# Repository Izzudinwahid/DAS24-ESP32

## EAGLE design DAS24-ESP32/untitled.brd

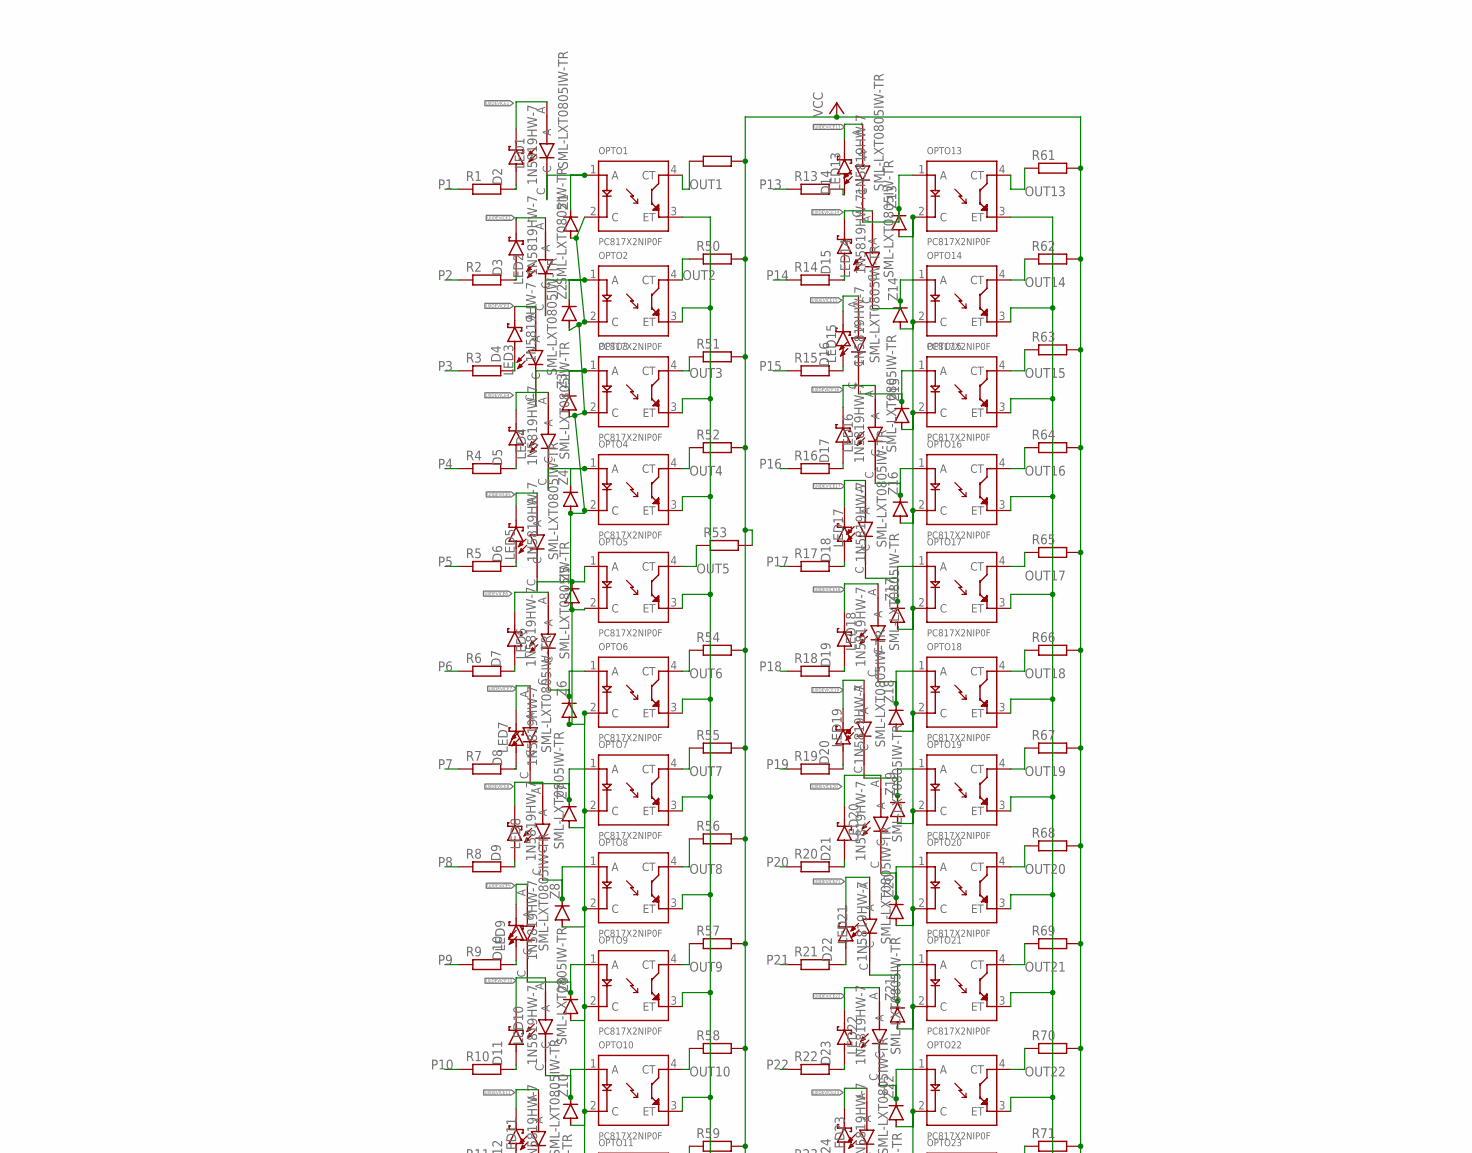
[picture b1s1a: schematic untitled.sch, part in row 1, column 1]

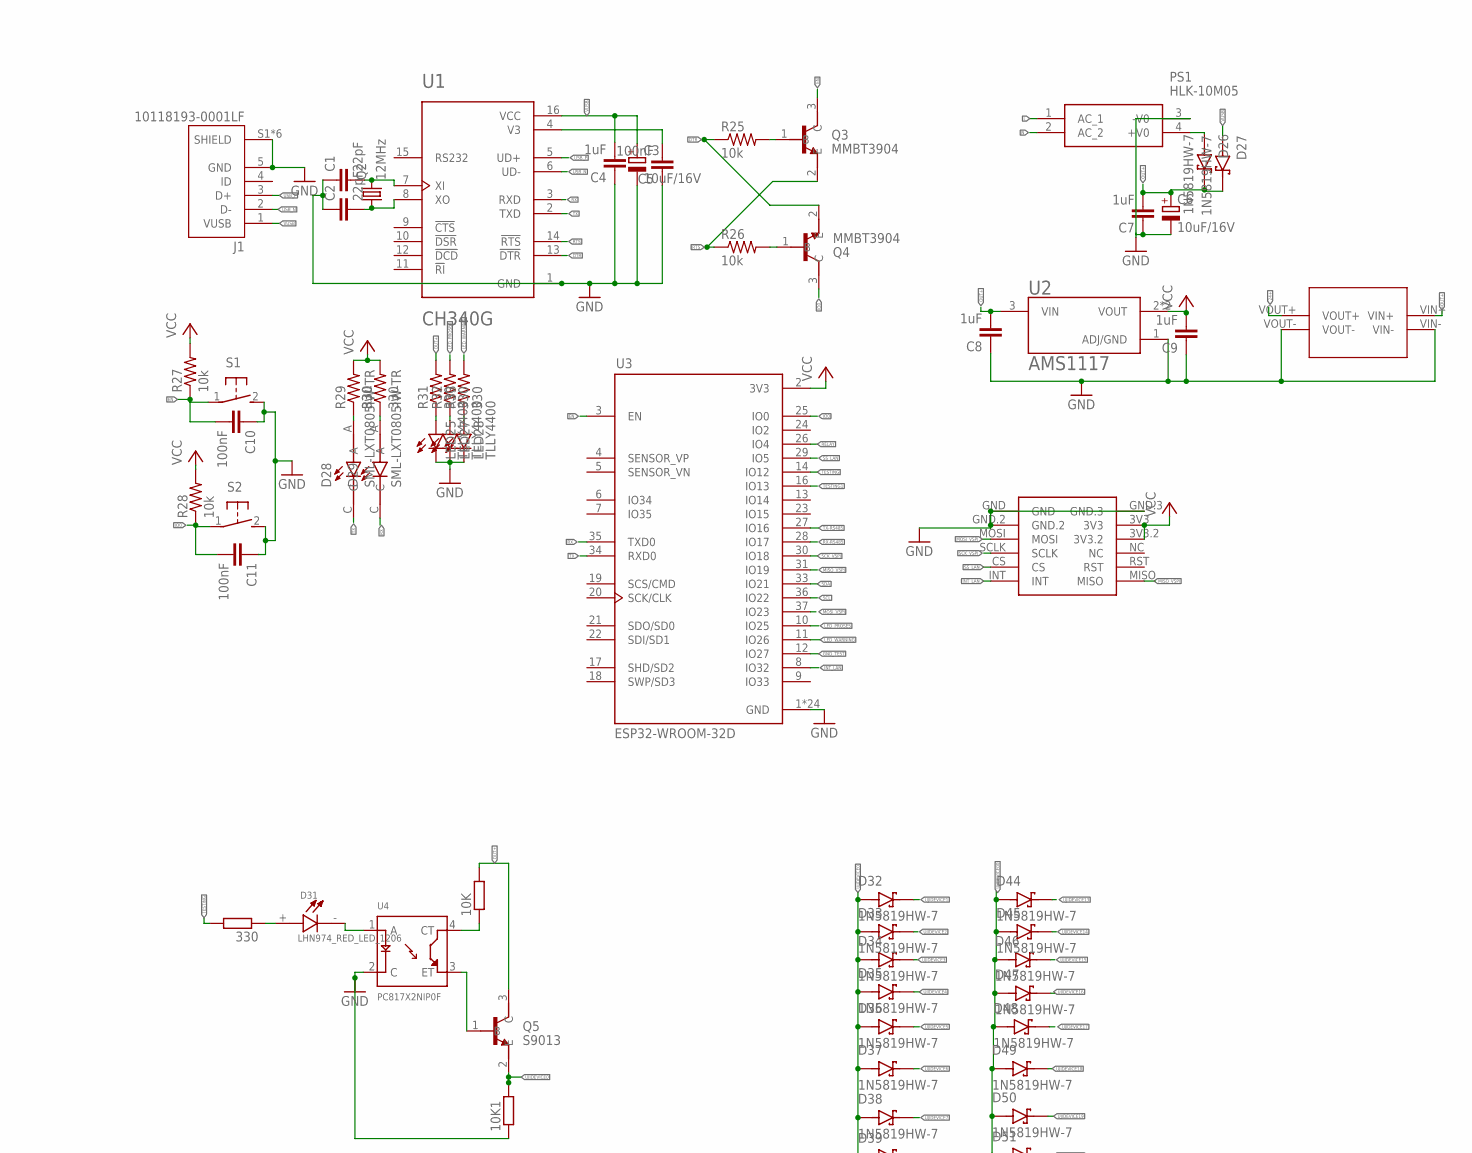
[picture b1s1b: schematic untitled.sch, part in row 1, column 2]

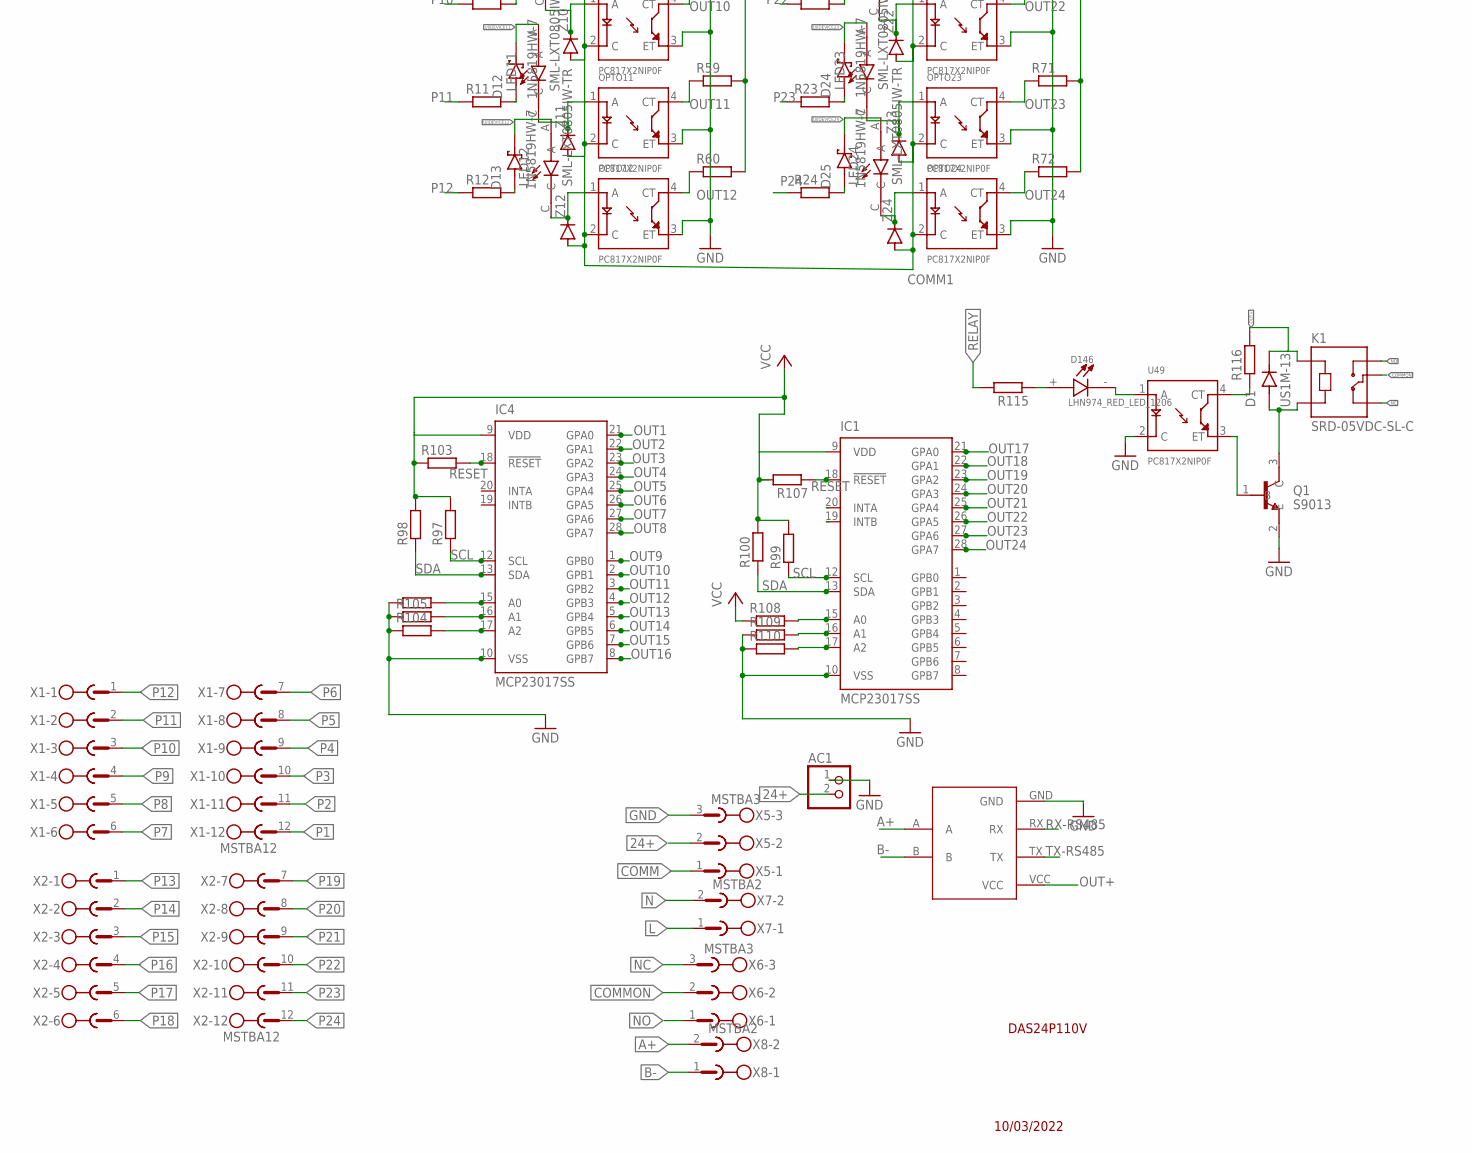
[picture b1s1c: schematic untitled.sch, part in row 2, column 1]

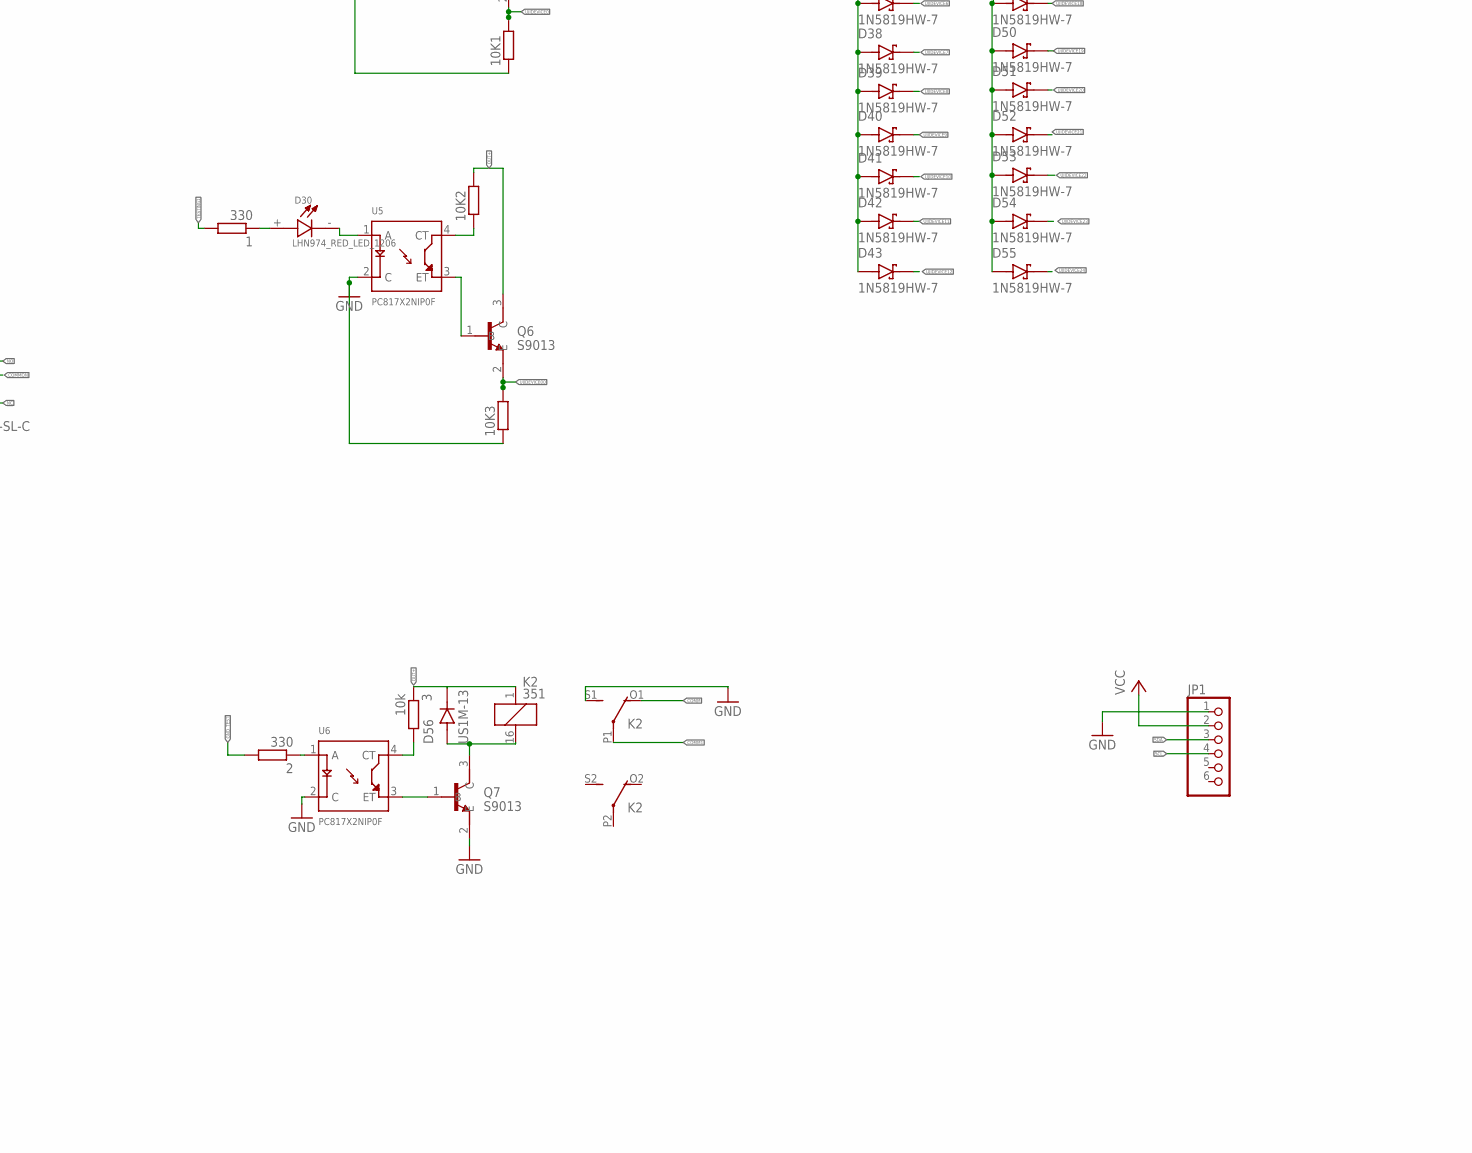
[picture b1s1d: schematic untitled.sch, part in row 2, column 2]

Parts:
1, 2: 330; R0805
3: 10k; R0805
10K, 10K1, 10K2, 10K3, 330: R-EU_R0805; R0805
AC1: PINHD-1X2; 1X02
C1, C2: 22pF; C0805K
C3, C6: 10uF/16V; 153CLV-0505
C4, C7, C8, C9: 1uF; C0805K
C5, C10, C11: 100nF; C0805K
D1, D56: US1M-13; DIOM5226X240N
D2, D3, D4, D5, D6, D7, D8, D9, D10, D11, D12, D13, D14, D15, D16, D17, D18, D19, D20, D21, D22, D23, D24, D25, D26, D27, D32, D33, D34, D35, D36, D37, D38, D39, D40, D41, D42, D43, D44, D45, D46, D47, D48, D49, D50, D51, D52, D53, D54, D55: 1N5819HW-7; SOD3715X145N
D28, D29: SML-LXT0805IW-TR; LEDC2012X120N
D30, D31, D146: LHN974_RED_LED_1206; LEDC3216X120N
IC1, IC4: MCP23017SS; SSOP28DB
J1: 10118193-0001LF; FCI_10118193-0001LF
JP1: PINHD-1X6CLEAN; 1X06-CLEAN
K1: SRD-05VDC-SL-C; RELAY_SRD-05VDC-SL-C
K2: 351
LED1, LED2, LED3, LED4, LED5, LED6, LED7, LED8, LED9, LED10, LED11, LED12, LED13, LED14, LED15, LED16, LED17, LED18, LED19, LED20, LED21, LED22, LED23, LED24: SML-LXT0805IW-TR; LEDC2012X120N
LED25, LED27, LED28: TLLY4400; LED3MM
MT1: MT3608
OPTO1, OPTO2, OPTO3, OPTO4, OPTO5, OPTO6, OPTO7, OPTO8, OPTO9, OPTO10, OPTO11, OPTO12, OPTO13, OPTO14, OPTO15, OPTO16, OPTO17, OPTO18, OPTO19, OPTO20, OPTO21, OPTO22, OPTO23, OPTO24: PC817X2NIP0F; SOT254P975X400-4N
PS1: HLK-10M05; HLK10M05
Q1, Q5, Q6, Q7: S9013; SOT95P240X120-3N
Q2: 12MHz; SM49
Q3, Q4: MMBT3904; SOT95P240X120-3N
R1, R2, R3, R4, R5, R6, R7, R8, R9, R10, R11, R12, R13, R14, R15, R16, R17, R18, R19, R20, R21, R22, R23, R24: R-EU_0414/15; 0414/15
R25, R26, R27, R28: 10k; M0805
R29, R30, R31, R32, R33: 330; M0805
R49, R50, R51, R52, R53, R54, R55, R56, R57, R58, R59, R60, R61, R62, R63, R64, R65, R66, R67, R68, R69, R70, R71, R72, R97, R98, R99, R100, R103, R104, R105, R106, R107, R108, R109, R110, R115, R116: R-EU_R0805; R0805
S1, S2: 31-XX; B3F-31XX
TTL-RS1: TTL-RS485
U1: CH340G; SOIC127P600X180-16N
U2: AMS1117; SOT229P700X180-4N
U3: ESP32-WROOM-32D; MODULE_ESP32-WROOM-32D
U4, U5, U6, U49: PC817X2NIP0F; SOT254P975X400-4N
U$1: MINI_W5500
X1, X2: MSTBA12
X5, X6: MSTBA3
X7, X8: MSTBA2
Z1, Z2, Z3, Z4, Z5, Z6, Z7, Z8, Z9, Z10, Z11, Z12, Z13, Z14, Z15, Z16, Z17, Z18, Z19, Z20, Z21, Z22, Z23, Z24: DIODE-SOD123; SOD123

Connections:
24+: AC1.2, MT1.VOUT+, X5.2
A+: TTL-RS1.A, X8.2
B-: TTL-RS1.B, X8.1
COMM: K2.O1 (O), X5.1
COMM1: K2.P1, OPTO1.2 (C), OPTO2.2 (C), OPTO3.2 (C), OPTO4.2 (C), OPTO5.2 (C), OPTO6.2 (C), OPTO7.2 (C), OPTO8.2 (C), OPTO9.2 (C), OPTO10.2 (C), OPTO11.2 (C), OPTO12.2 (C), OPTO13.2 (C), OPTO14.2 (C), OPTO15.2 (C), OPTO16.2 (C), OPTO17.2 (C), OPTO18.2 (C), OPTO19.2 (C), OPTO20.2 (C), OPTO21.2 (C), OPTO22.2 (C), OPTO23.2 (C), OPTO24.2 (C), Z1.A, Z2.A, Z3.A, Z4.A, Z5.A, Z6.A, Z7.A, Z8.A, Z9.A, Z10.A, Z11.A, Z12.A, Z13.A, Z14.A, Z15.A, Z16.A, Z17.A, Z18.A, Z19.A, Z20.A, Z21.A, Z22.A, Z23.A, Z24.A
COMMON: K1.COM, X6.2
DTR: Q4.2 (E), R25.1, U1.13 (!DTR)
EN: C10.2, Q3.3 (C), R27.1, S1.1, U3.3 (EN)
GND: 10K1.1, 10K3.1, AC1.1, C1.1, C2.1, C3.-, C4.1, C5.1, C6.-, C7.1, C8.1, C9.1, C10.1, C11.1, IC1.10 (VSS), IC4.10 (VSS), J1.5 (GND), J1.S1 (SHIELD), J1.S2 (SHIELD), J1.S3 (SHIELD), J1.S4 (SHIELD), J1.S5 (SHIELD), J1.S6 (SHIELD), JP1.1, K2.S1 (S), LED25.K (C), LED27.K (C), LED28.K (C), MT1.VIN-, MT1.VOUT-, OPTO1.3 (ET), OPTO2.3 (ET), OPTO3.3 (ET), OPTO4.3 (ET), OPTO5.3 (ET), OPTO6.3 (ET), OPTO7.3 (ET), OPTO8.3 (ET), OPTO9.3 (ET), OPTO10.3 (ET), OPTO11.3 (ET), OPTO12.3 (ET), OPTO13.3 (ET), OPTO14.3 (ET), OPTO15.3 (ET), OPTO16.3 (ET), OPTO17.3 (ET), OPTO18.3 (ET), OPTO19.3 (ET), OPTO20.3 (ET), OPTO21.3 (ET), OPTO22.3 (ET), OPTO23.3 (ET), OPTO24.3 (ET), PS1.3 (-V0), Q1.2 (E), Q7.2 (E), R104.1, R105.1, R106.1, R109.1, R110.1, S1.2 (S), S2.2 (S), TTL-RS1.GND, U1.1 (GND), U2.1 (ADJ/GND), U3.1 (GND), U3.15 (GND), U3.38 (GND), U3.39_1 (GND), U3.39_2 (GND), U3.39_3 (GND), U3.39_4 (GND), U3.39_5 (GND), U3.39_6 (GND), U3.39_7 (GND), U3.39_8 (GND), U3.39_9 (GND), U3.39_10 (GND), U3.39_11 (GND), U3.39_12 (GND), U3.39_13 (GND), U3.39_14 (GND), U3.39_15 (GND), U3.39_16 (GND), U3.39_17 (GND), U3.39_18 (GND), U3.39_19 (GND), U3.39_20 (GND), U3.39_21 (GND), U4.2 (C), U5.2 (C), U6.2 (C), U49.2 (C), U$1.GND, U$1.GND.2, U$1.GND.3, X5.3
GND_TEST: 2.2, U3.12 (IO27)
INT_LAN: U3.8 (IO32), U$1.INT
IO0: C11.2, Q4.3 (C), R28.1, S2.1, U3.25 (IO0)
L: PS1.1 (AC_1), X7.1
LED_PROSES: R32.2, U3.10 (IO25)
LED_WARNING: R33.2, U3.11 (IO26)
MISO_VSPI: U3.31 (IO19), U$1.MISO
MOSI_VSPI: U3.37 (IO23), U$1.MOSI
N: PS1.2 (AC_2), X7.2
unnamed: D2.A, R1.2
unnamed: LED10.C, OPTO10.1 (A), Z10.C
unnamed: D3.A, R2.2
unnamed: D4.A, R3.2
unnamed: LED1.C, OPTO1.1 (A), Z1.C
unnamed: D5.A, R4.2
unnamed: LED27.A, R32.1
unnamed: D6.A, R5.2
unnamed: LED28.A, R33.1
unnamed: D7.A, R6.2
unnamed: LED2.C, OPTO2.1 (A), Z2.C
unnamed: D8.A, R7.2
unnamed: 2.1, U6.1 (A)
unnamed: D9.A, R8.2
unnamed: LED3.C, OPTO3.1 (A), Z3.C
unnamed: D15.A, R14.2
unnamed: 3.2, U6.4 (CT)
unnamed: LED4.C, OPTO4.1 (A), Z4.C
unnamed: D10.A, R9.2
unnamed: LED5.C, OPTO5.1 (A), Z5.C
unnamed: D56.A, K2.16 (2), Q7.3 (C)
unnamed: D11.A, R10.2
unnamed: Q7.1 (B), U6.3 (ET)
unnamed: LED6.C, OPTO6.1 (A), Z6.C
unnamed: C1.2, Q2.2, U1.7 (XI)
unnamed: D12.A, R11.2
unnamed: C2.2, Q2.1, U1.8 (XO)
unnamed: Q3.1 (B), R25.2
unnamed: C5.2, U1.4 (V3)
unnamed: Q4.1 (B), R26.2
unnamed: D26.A, PS1.4 (+V0)
unnamed: 330.1, D31.+
unnamed: D13.A, R12.2
unnamed: LED25.A, R31.1
unnamed: D28.A, R29.1
unnamed: D29.A, R30.1
unnamed: D14.A, R13.2
unnamed: 1.1, D30.+
unnamed: D31.-, U4.1 (A)
unnamed: 10K.1, U4.4 (CT)
unnamed: D16.A, R15.2
unnamed: Q5.1 (B), U4.3 (ET)
unnamed: D30.-, U5.1 (A)
unnamed: 10K2.1, U5.4 (CT)
unnamed: D17.A, R16.2
unnamed: D18.A, R17.2
unnamed: D19.A, R18.2
unnamed: D20.A, R19.2
unnamed: D21.A, R20.2
unnamed: LED7.C, OPTO7.1 (A), Z7.C
unnamed: D22.A, R21.2
unnamed: LED8.C, OPTO8.1 (A), Z8.C
unnamed: LED9.C, OPTO9.1 (A), Z9.C
unnamed: LED11.C, OPTO11.1 (A), Z11.C
unnamed: LED12.C, OPTO12.1 (A), Z12.C
unnamed: D23.A, R22.2
unnamed: LED13.C, OPTO13.1 (A), Z13.C
unnamed: LED14.C, OPTO14.1 (A), Z14.C
unnamed: LED15.C, OPTO15.1 (A), Z15.C
unnamed: D24.A, R23.2
unnamed: LED16.C, OPTO16.1 (A), Z16.C
unnamed: LED17.C, OPTO17.1 (A), Z17.C
unnamed: LED18.C, OPTO18.1 (A), Z18.C
unnamed: D25.A, R24.2
unnamed: LED19.C, OPTO19.1 (A), Z19.C
unnamed: LED20.C, OPTO20.1 (A), Z20.C
unnamed: LED21.C, OPTO21.1 (A), Z21.C
unnamed: LED22.C, OPTO22.1 (A), Z22.C
unnamed: LED23.C, OPTO23.1 (A), Z23.C
unnamed: LED24.C, OPTO24.1 (A), Z24.C
unnamed: Q6.1 (B), U5.3 (ET)
unnamed: D146.-, U49.1 (A)
unnamed: D146.+, R115.1
unnamed: R116.1, U49.4 (CT)
unnamed: D1.A, K1.A2, Q1.3 (C)
unnamed: Q1.1 (B), U49.3 (ET)
unnamed: IC1.15 (A0), R108.2
unnamed: IC1.16 (A1), R109.2
unnamed: IC4.15 (A0), R106.2
unnamed: IC4.16 (A1), R105.2
unnamed: IC4.17 (A2), R104.2
unnamed: IC1.17 (A2), R110.2
NC: K1.NC, X6.3
NO: K1.NO, X6.1
OUT1: IC4.21 (GPA0), OPTO1.4 (CT), R49.1
OUT2: IC4.22 (GPA1), OPTO2.4 (CT), R50.1
OUT3: IC4.23 (GPA2), OPTO3.4 (CT), R51.1
OUT4: IC4.24 (GPA3), OPTO4.4 (CT), R52.1
OUT5: IC4.25 (GPA4), OPTO5.4 (CT), R53.1
OUT6: IC4.26 (GPA5), OPTO6.4 (CT), R54.1
OUT7: IC4.27 (GPA6), OPTO7.4 (CT), R55.1
OUT8: IC4.28 (GPA7), OPTO8.4 (CT), R56.1
OUT9: IC4.1 (GPB0), OPTO9.4 (CT), R57.1
OUT10: IC4.2 (GPB1), OPTO10.4 (CT), R58.1
OUT11: IC4.3 (GPB2), OPTO11.4 (CT), R59.1
OUT12: IC4.4 (GPB3), OPTO12.4 (CT), R60.1
OUT13: IC4.5 (GPB4), OPTO13.4 (CT), R61.1
OUT14: IC4.6 (GPB5), OPTO14.4 (CT), R62.1
OUT15: IC4.7 (GPB6), OPTO15.4 (CT), R63.1
OUT16: IC4.8 (GPB7), OPTO16.4 (CT), R64.1
OUT17: IC1.21 (GPA0), OPTO17.4 (CT), R65.1
OUT18: IC1.22 (GPA1), OPTO18.4 (CT), R66.1
OUT19: IC1.23 (GPA2), OPTO19.4 (CT), R67.1
OUT20: IC1.24 (GPA3), OPTO20.4 (CT), R68.1
OUT21: IC1.25 (GPA4), OPTO21.4 (CT), R69.1
OUT22: IC1.26 (GPA5), OPTO22.4 (CT), R70.1
OUT23: IC1.27 (GPA6), OPTO23.4 (CT), R71.1
OUT24: IC1.28 (GPA7), OPTO24.4 (CT), R72.1
OUT+: 3.1, 10K.2, 10K2.2, C6.+, C7.2, C8.2, D1.C (K), D26.C (K), D27.C (K), D56.C (K), K1.A1, K2.1, MT1.VIN+, Q5.3 (C), Q6.3 (C), R31.2, R116.2, TTL-RS1.VCC, U2.3 (VIN)
P1: R1.1, X1.12
P2: R2.1, X1.11
P3: R3.1, X1.10
P4: R4.1, X1.9
P5: R5.1, X1.8
P6: R6.1, X1.7
P7: R7.1, X1.6
P8: R8.1, X1.5
P9: R9.1, X1.4
P10: R10.1, X1.3
P11: R11.1, X1.2
P12: R12.1, X1.1
P13: R13.1, X2.1
P14: R14.1, X2.2
P15: R15.1, X2.3
P16: R16.1, X2.4
P17: R17.1, X2.5
P18: R18.1, X2.6
P19: R19.1, X2.7
P20: R20.1, X2.8
P21: R21.1, X2.9
P22: R22.1, X2.10
P23: R23.1, X2.11
P24: R24.1, X2.12
RELAY: R115.2, U3.26 (IO4)
RESET: IC1.18 (!RESET), IC4.18 (!RESET), R103.2, R107.1
RTS: Q3.2 (E), R26.1, U1.14 (!RTS)
RX: D29.C, U1.3 (RXD), U3.35 (TXD0)
RX-RS485: TTL-RS1.RX, U3.28 (IO17)
SCK_VSPI: U3.30 (IO18), U$1.SCLK
SCL: IC1.12 (SCL), IC4.12 (SCL), JP1.4, R97.1, R99.1, U3.36 (IO22)
SDA: IC1.13 (SDA), IC4.13 (SDA), JP1.3, R98.1, R100.1, U3.33 (IO21)
SS_LAN: U3.29 (IO5), U$1.CS
TESTING: 330.2, U3.14 (IO12)
TESTING1: 1.2, U3.16 (IO13)
TX: D28.C, U1.2 (TXD), U3.34 (RXD0)
TX-RS485: TTL-RS1.TX, U3.27 (IO16)
UJIDEVICE0: 10K1.2, D32.A, D33.A, D34.A, D35.A, D36.A, D37.A, D38.A, D39.A, D40.A, D41.A, D42.A, D43.A, Q5.2 (E)
UJIDEVICE00: 10K3.2, D44.A, D45.A, D46.A, D47.A, D48.A, D49.A, D50.A, D51.A, D52.A, D53.A, D54.A, D55.A, Q6.2 (E)
UJIDEVICE1: D2.C (K), D32.C (K), LED1.A
UJIDEVICE2: D3.C (K), D33.C (K), LED2.A
UJIDEVICE3: D4.C (K), D34.C (K), LED3.A
UJIDEVICE4: D5.C (K), D35.C (K), LED4.A
UJIDEVICE5: D6.C (K), D36.C (K), LED5.A
UJIDEVICE6: D7.C (K), D37.C (K), LED6.A
UJIDEVICE7: D8.C (K), D38.C (K), LED7.A
UJIDEVICE8: D9.C (K), D39.C (K), LED8.A
UJIDEVICE9: D10.C (K), D40.C (K), LED9.A
UJIDEVICE10: D11.C (K), D41.C (K), LED10.A
UJIDEVICE11: D12.C (K), D42.C (K), LED11.A
UJIDEVICE12: D13.C (K), D43.C (K), LED12.A
UJIDEVICE13: D14.C (K), D44.C (K), LED13.A
UJIDEVICE14: D15.C (K), D45.C (K), LED14.A
UJIDEVICE15: D16.C (K), D46.C (K), LED15.A
UJIDEVICE16: D17.C (K), D47.C (K), LED16.A
UJIDEVICE17: D18.C (K), D48.C (K), LED17.A
UJIDEVICE18: D19.C (K), D49.C (K), LED18.A
UJIDEVICE19: D20.C (K), D50.C (K), LED19.A
UJIDEVICE20: D21.C (K), D51.C (K), LED20.A
UJIDEVICE21: D22.C (K), D52.C (K), LED21.A
UJIDEVICE22: D23.C (K), D53.C (K), LED22.A
UJIDEVICE23: D24.C (K), D54.C (K), LED23.A
UJIDEVICE24: D25.C (K), D55.C (K), LED24.A
USB_N: J1.2 (D-), U1.6 (UD-)
USB_P: J1.3 (D+), U1.5 (UD+)
VCC: C9.2, IC1.9 (VDD), IC4.9 (VDD), JP1.2, R27.2, R28.2, R29.2, R30.2, R49.2, R50.2, R51.2, R52.2, R53.2, R54.2, R55.2, R56.2, R57.2, R58.2, R59.2, R60.2, R61.2, R62.2, R63.2, R64.2, R65.2, R66.2, R67.2, R68.2, R69.2, R70.2, R71.2, R72.2, R97.2, R98.2, R99.2, R100.2, R103.1, R107.2, R108.1, U2.2 (VOUT), U2.4 (VOUT), U3.2 (3V3), U$1.3V3, U$1.3V3.2
VUSB: C3.+, C4.2, D27.A, J1.1 (VUSB), U1.16 (VCC)

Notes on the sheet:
DAS24P110V
10/03/2022

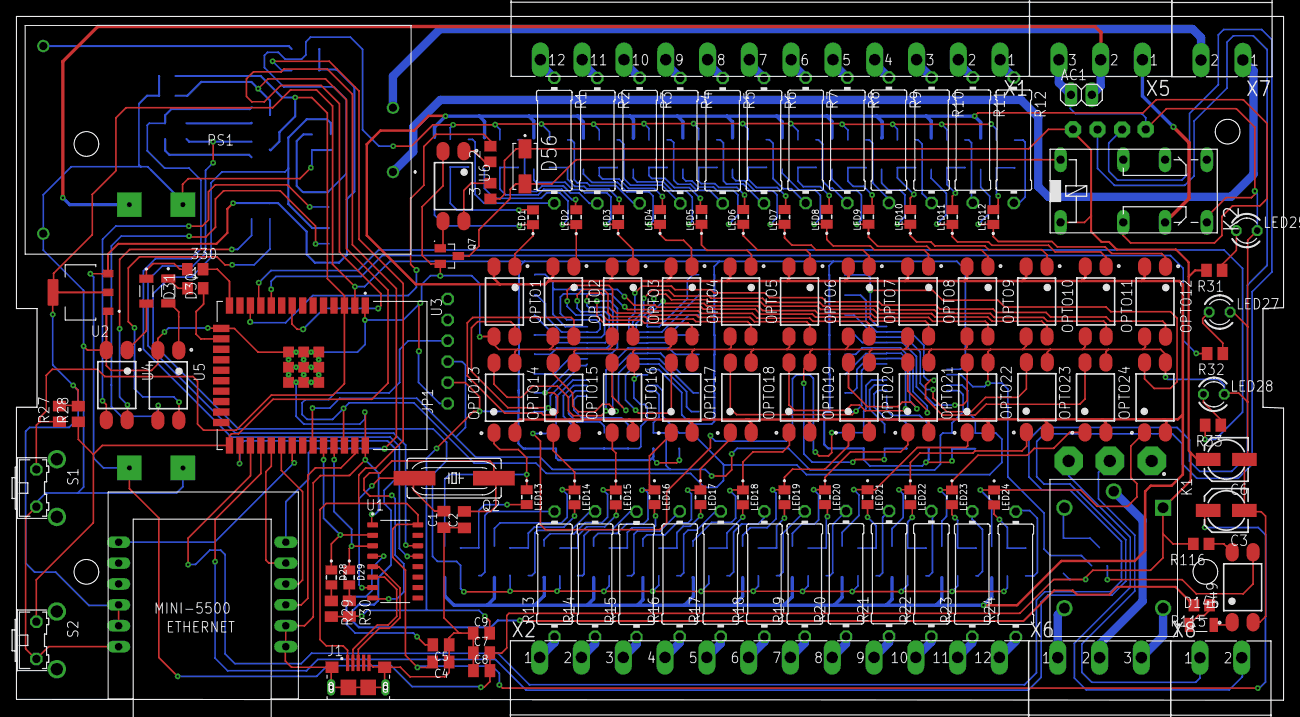
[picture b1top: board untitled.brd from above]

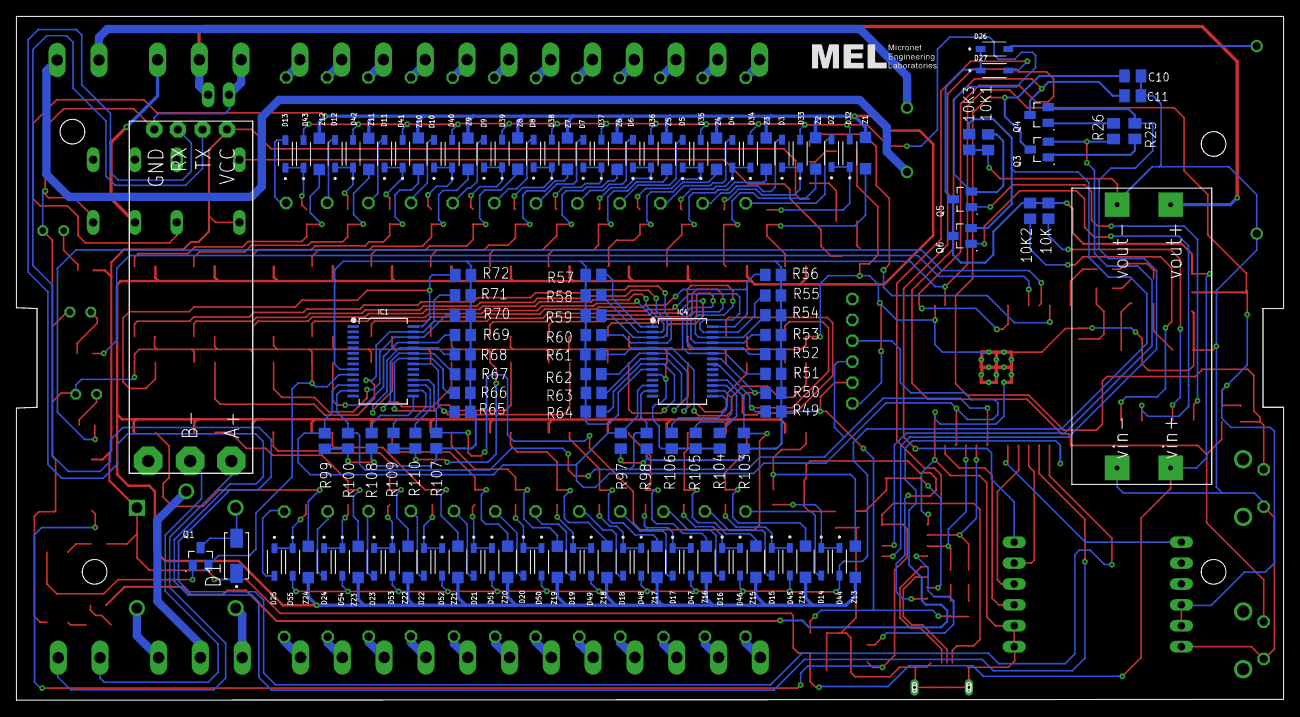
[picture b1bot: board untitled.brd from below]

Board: 2 copper layers, 154.0 x 83.1 mm, 255 parts (128 on the bottom side), 194 nets.

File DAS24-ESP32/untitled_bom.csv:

Comment,Designator,Footprint,LCSC Part #
,AC1,1X02,
,JP1,1X06-CLEAN,
,R1,0414/15,
,R2,0414/15,
,R3,0414/15,
,R4,0414/15,
,R5,0414/15,
,R6,0414/15,
,R7,0414/15,
,R8,0414/15,
,R9,0414/15,
,R10,0414/15,
,R11,0414/15,
,R12,0414/15,
,R13,0414/15,
,R14,0414/15,
,R15,0414/15,
,R16,0414/15,
,R17,0414/15,
,R18,0414/15,
,R19,0414/15,
,R20,0414/15,
,R21,0414/15,
,R22,0414/15,
,R23,0414/15,
,R24,0414/15,
,S1,B3F-31XX,
,S2,B3F-31XX,
,MT1,MT3608,
,10K,R0805,
,10K1,R0805,
,10K2,R0805,
,10K3,R0805,
,330,R0805,
,R49,R0805,
,R50,R0805,
,R51,R0805,
,R52,R0805,
,R53,R0805,
,R54,R0805,
,R55,R0805,
,R56,R0805,
,R57,R0805,
,R58,R0805,
,R59,R0805,
,R60,R0805,
,R61,R0805,
,R62,R0805,
,R63,R0805,
,R64,R0805,
,R65,R0805,
,R66,R0805,
,R67,R0805,
,R68,R0805,
,R69,R0805,
,R70,R0805,
,R71,R0805,
,R72,R0805,
,R97,R0805,
,R98,R0805,
,R99,R0805,
,R100,R0805,
,R103,R0805,
,R104,R0805,
,R105,R0805,
,R106,R0805,
,R107,R0805,
,R108,R0805,
,R109,R0805,
,R110,R0805,
,R115,R0805,
,R116,R0805,
,Z1,SOD123,
,Z2,SOD123,
,Z3,SOD123,
,Z4,SOD123,
,Z5,SOD123,
,Z6,SOD123,
,Z7,SOD123,
,Z8,SOD123,
,Z9,SOD123,
,Z10,SOD123,
,Z11,SOD123,
,Z12,SOD123,
,Z13,SOD123,
,Z14,SOD123,
,Z15,SOD123,
,Z16,SOD123,
,Z17,SOD123,
,Z18,SOD123,
,Z19,SOD123,
,Z20,SOD123,
,Z21,SOD123,
,Z22,SOD123,
,Z23,SOD123,
,Z24,SOD123,
,TTL-RS1,TTL-RS485,
1N5819HW-7,D2 D3 D4 D5 D6 D7 D8 D9 D10 D11 D12 D13 D14 D15 D16 D17 D18 D19 D20 D21 D22 D23 D24 D25 D26 D27 D32 D33 D34 D35 D36 D37 D38 D39 D40 D41 D42 D43 D44 D45 D46 D47 D48 D49 D50 D51 D52 D53 D54 D55,SOD3715X145N,
1uF,C4 C7 C8 C9,C0805K,
10k,R25 R26 R27 R28,M0805,
10k,3,R0805,
10uF/16V,C3 C6,153CLV-0505,
12MHz,Q2,SM49,
22pF,C1 C2,C0805K,
100nF,C5 C10 C11,C0805K,
330,R29 R30 R31 R32 R33,M0805,
330,1 2,R0805,
351,K2,351,
10118193-0001LF,J1,FCI_10118193-0001LF,
AMS1117,U2,SOT229P700X180-4N,
CH340G,U1,SOIC127P600X180-16N,
ESP32-WROOM-32D,U3,MODULE_ESP32-WROOM-32D,
HLK-10M05,PS1,HLK10M05,
LHN974_RED_LED_1206,D30 D31 D146,LEDC3216X120N,
MCP23017SS,IC1 IC4,SSOP28DB,
MINI_W5500,U$1,MINI_W5500,
MMBT3904,Q3 Q4,SOT95P240X120-3N,
MSTBA2,X7 X8,MSTBA2,
MSTBA3,X5 X6,MSTBA3,
MSTBA12,X1 X2,MSTBA12,
PC817X2NIP0F,OPTO1 OPTO2 OPTO3 OPTO4 OPTO5 OPTO6 OPTO7 OPTO8 OPTO9 OPTO10 OPTO11 OPTO12 OPTO13 OPTO14 OPTO15 OPTO16 OPTO17 OPTO18 OPTO19 OPTO20 OPTO21 OPTO22 OPTO23 OPTO24 U4 U5 U6 U49,SOT254P975X400-4N,
S9013,Q1 Q5 Q6 Q7,SOT95P240X120-3N,
SML-LXT0805IW-TR,D28 D29 LED1 LED2 LED3 LED4 LED5 LED6 LED7 LED8 LED9 LED10 LED11 LED12 LED13 LED14 LED15 LED16 LED17 LED18 LED19 LED20 LED21 LED22 LED23 LED24,LEDC2012X120N,
SRD-05VDC-SL-C,K1,RELAY_SRD-05VDC-SL-C,
TLLY4400,LED25 LED27 LED28,LED3MM,
US1M-13,D1 D56,DIOM5226X240N,

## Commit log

2023-01-27 revisi tanggal 27/01/2023
2023-02-21 pengajuan das dan revisi 21/02/2023
